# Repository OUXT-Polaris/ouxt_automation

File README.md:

# What is this?

Automation pipeline for Maritime RobotX Challenge

# What can we do with this tools.

- Setup development environment with ansible.
- Setting and manage CI toolchain to the target repository.
- Generating documentation. etc...

If you want to know more?
Please read [here.](https://ouxt-polaris.github.io/ouxt_automation/)

Developed by [OUXT-Polaris](https://www.ouxt.jp/)

# Sponsor

Our activities are made possible thanks to the support of our sponsors.

Eight Knot

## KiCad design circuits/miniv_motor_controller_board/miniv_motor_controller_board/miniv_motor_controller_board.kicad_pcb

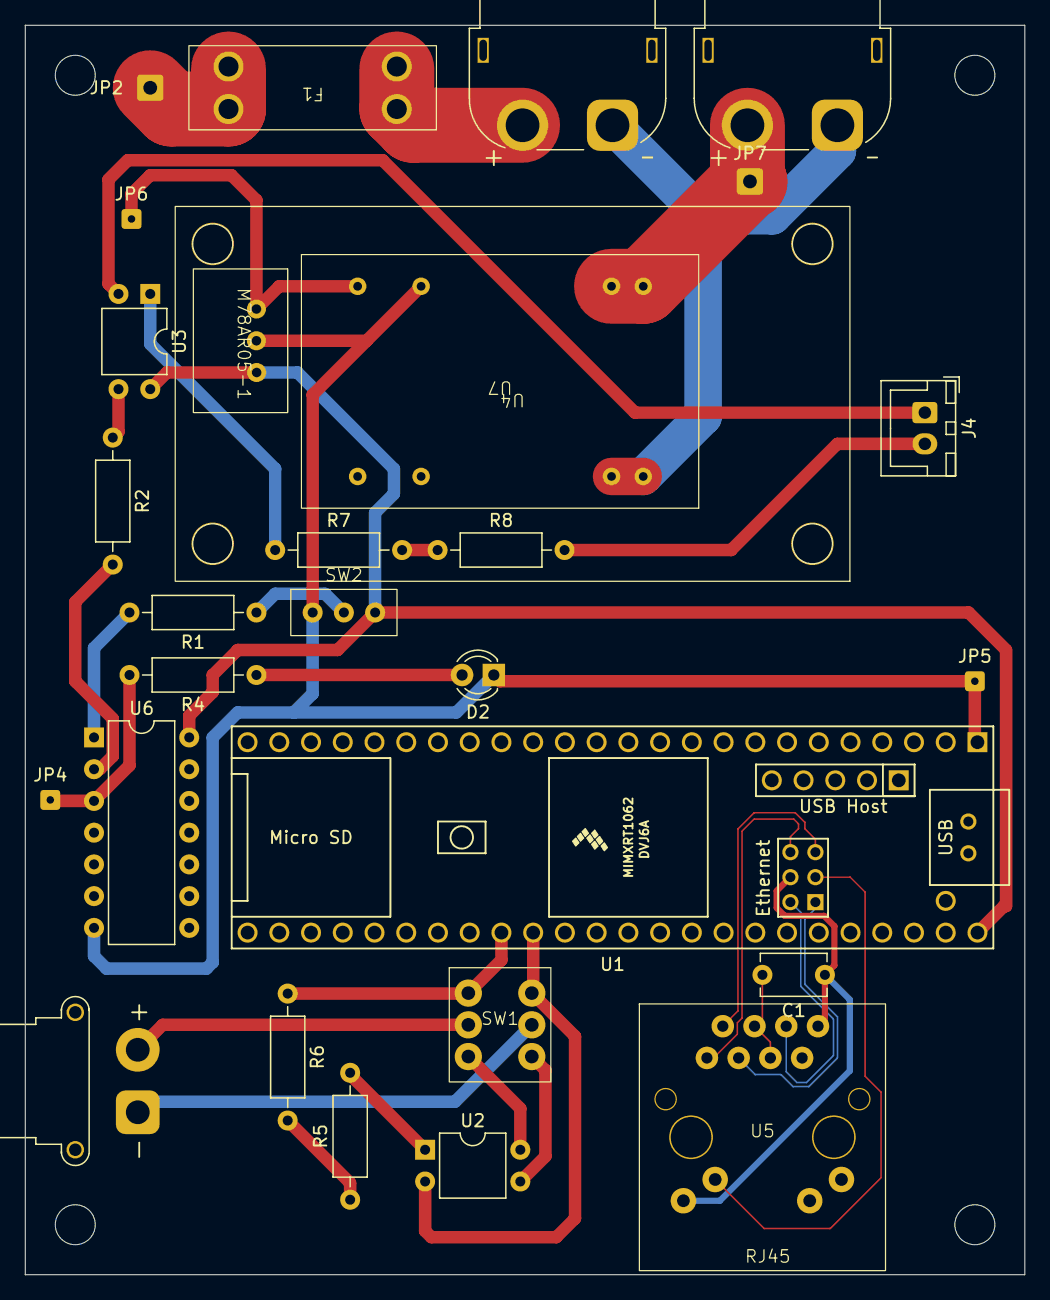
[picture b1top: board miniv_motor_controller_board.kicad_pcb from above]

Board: 2 copper layers, 80.0 x 100.0 mm, 33 parts (0 on the bottom side), 32 nets.

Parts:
C1: 0.1u; C_Disc_D5.1mm_W3.2mm_P5.00mm
D2: LED; LED_D3.0mm
F1: Fuse; 3557-15
H1, H2, H3, H4: MountingHole; MountingHole_3.2mm_M3
J1: DC_in; AMASS_XT60PW-F_1x02_P7.20mm_Horizontal
J2: T200_ESC_power; AMASS_XT60PW-F_1x02_P7.20mm_Horizontal
J3: T200_ESC_signal; AMASS_XT30PW-F_1x02_P2.50mm_Horizontal
J4: Conn_EStop_Signal; JST_XH_B2B-XH-A_1x02_P2.50mm_Vertical
JP2: Relay_NO; SolderWire-0.5sqmm_1x01_D0.9mm_OD2.1mm
JP4: Relay_SIG; SolderWire-0.1sqmm_1x01_D0.4mm_OD1mm
JP5: Relay_GND; SolderWire-0.1sqmm_1x01_D0.4mm_OD1mm
JP6: Relay_VCC; SolderWire-0.1sqmm_1x01_D0.4mm_OD1mm
JP7: Relay_COM; SolderWire-0.5sqmm_1x01_D0.9mm_OD2.1mm
M78AR05-1: M78AR05-1
R1, R2, R6, R7: 1K; R_Axial_DIN0207_L6.3mm_D2.5mm_P10.16mm_Horizontal
R4, R5, R8: 390; R_Axial_DIN0207_L6.3mm_D2.5mm_P10.16mm_Horizontal
SW1: SW_Push_DPDT; 2MD1-T2-B4-M2-Q-N
SW2: SW_disable_EStop; SS-12D00G3
U1: Teensy4.1; Teensy41
U2, U3: TLP624; DIP-4_W7.62mm
U4: AE-RELAY953B-12V
U5: RJLD-260YC1
U6: DIP-14_W7.62mm
U7: MIWI06-24S12

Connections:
+12V: JP6.1 (A), M78AR05-1.1 (Vin), U7.14 (+Vout)
GNDREF: D2.1 (K), JP5.1 (A), M78AR05-1.2 (GND), SW2.1 (A), U1.1 (GND), U6.7 (GND), U7.16 (-Vout)
GNDREF_Bat: J1.1, J2.1, U7.2 (-Vin), U7.3 (-Vin)
unnamed: C1.2, U5.4 (CT), U5.5 (CT)
unnamed: D2.2 (A), R4.1
unnamed: J1.2, JP7.1 (A), U7.22 (+Vin), U7.23 (+Vin)
unnamed: F1.1, J2.2
unnamed: J3.1, SW1.2 (B)
unnamed: J3.2, SW1.5 (B)
unnamed: J4.1, U3.2
unnamed: J4.2, R8.2
unnamed: F1.2, JP2.1 (A)
unnamed: JP4.1 (A), R4.2, U6.3 (1Y)
unnamed: M78AR05-1.3 (Vout), SW2.3 (C), U1.48 (VIN), U3.4, U6.14 (Vcc)
unnamed: R2.1, U3.3
unnamed: R5.1, R6.2
unnamed: R5.2, U2.1
unnamed: R7.1, U3.1
unnamed: R7.2, R8.1
unnamed: SW1.1 (A), U1.34 (GND), U2.2
unnamed: SW1.3 (C), U2.3
unnamed: SW1.6 (C), U2.4
unnamed: R1.1, SW2.2 (B)
unnamed: R6.1, SW1.4 (A), U1.33 (41_A17)
unnamed: U1.61 (LED), U5.10
unnamed: U1.60 (R+), U5.3 (RD+)
unnamed: U1.65 (R-), U5.6 (RD-)
unnamed: U1.63 (T+), U5.1 (TD+)
unnamed: U1.62 (T-), U5.2 (TD-)
unnamed: C1.1, U1.64 (GND), U5.8 (GND), U5.9
unnamed: R1.2, U6.1 (1A)
unnamed: R2.2, U6.2 (1B)

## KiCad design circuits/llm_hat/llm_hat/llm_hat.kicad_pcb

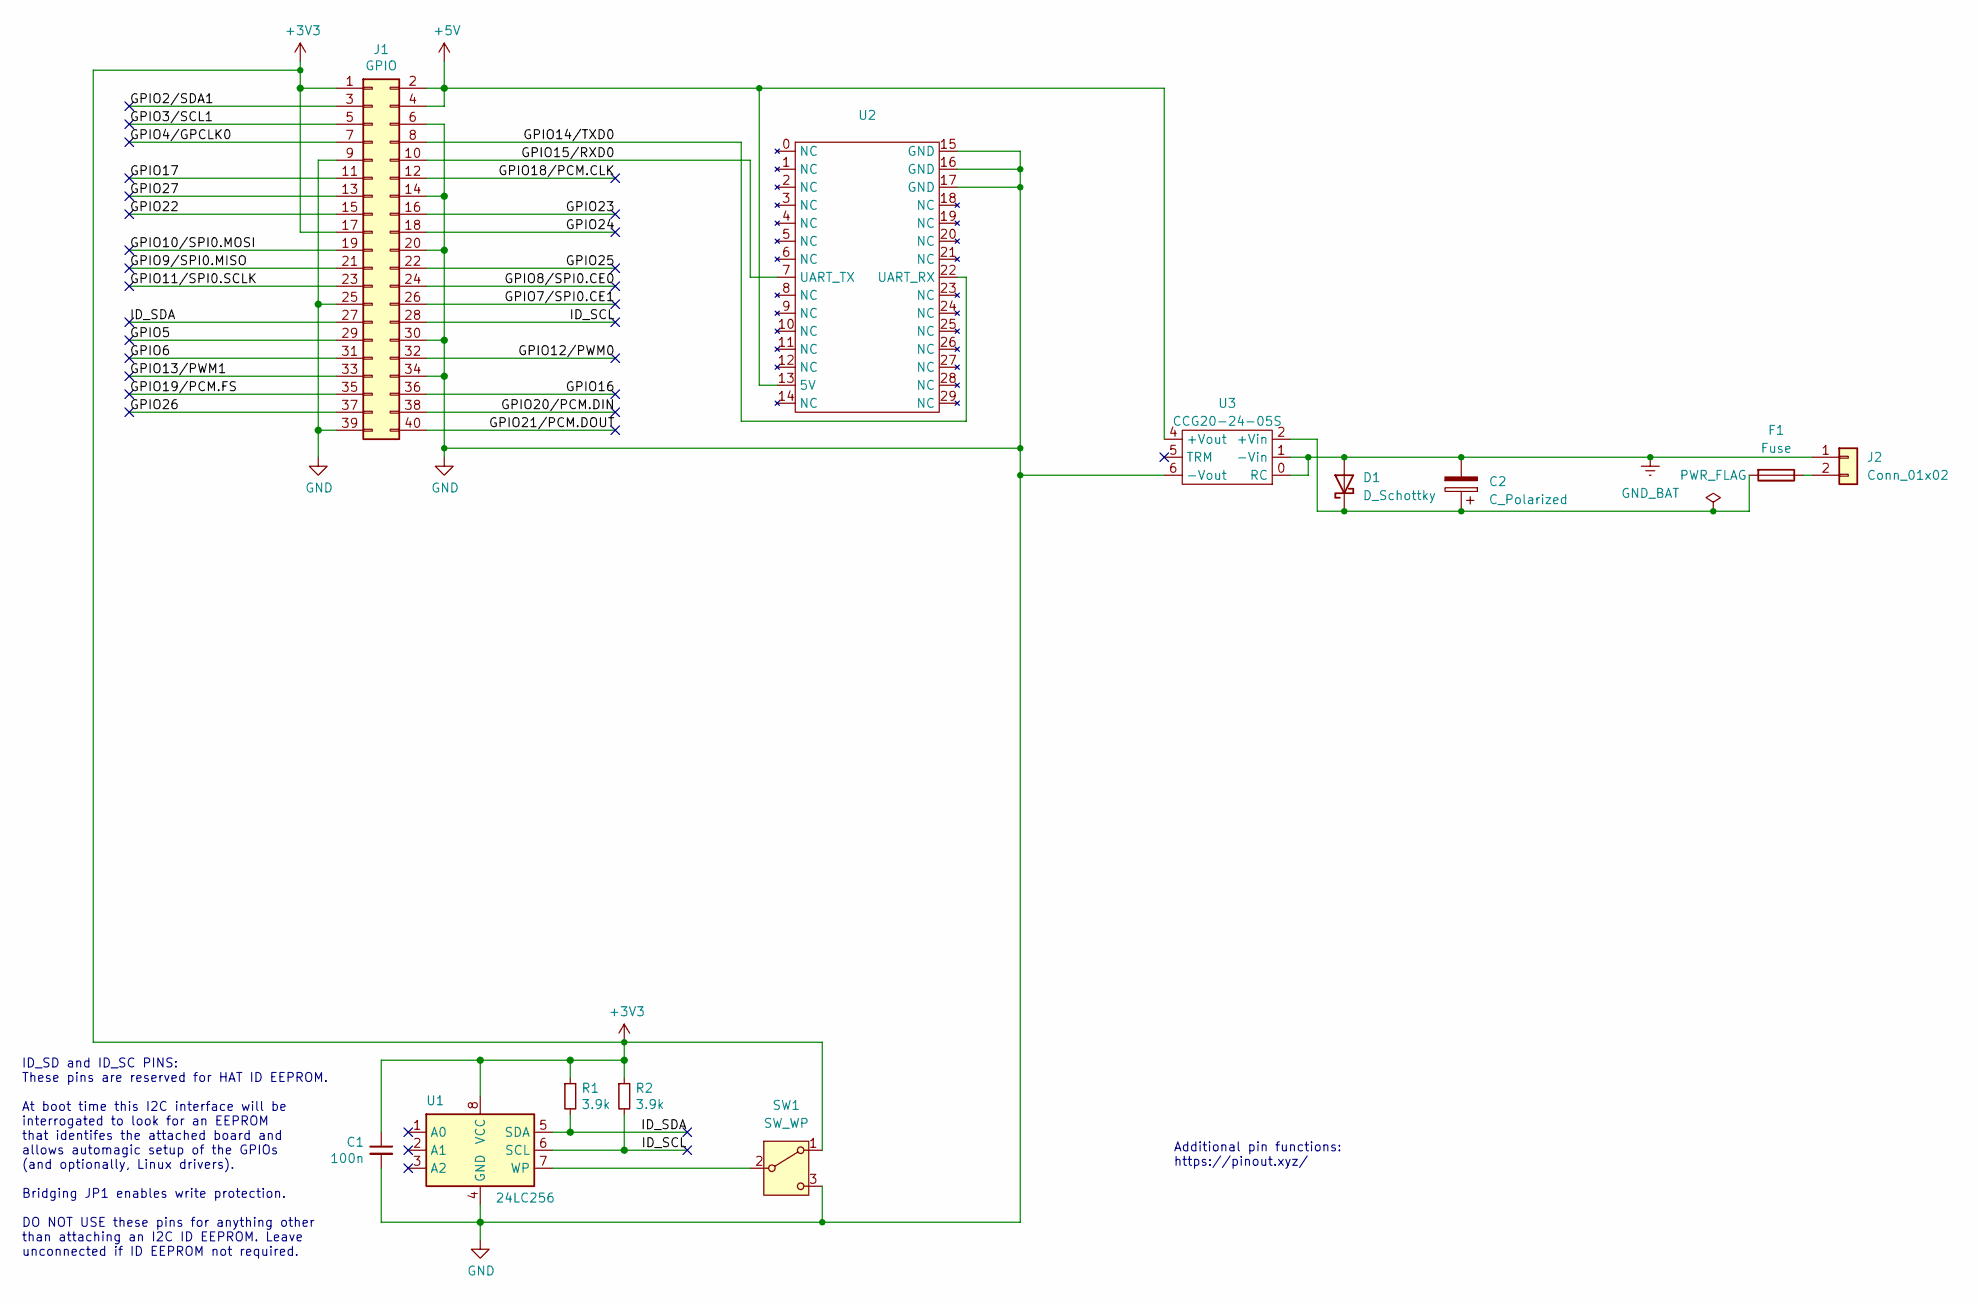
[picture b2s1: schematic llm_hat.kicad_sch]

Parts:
C1: 100n; C_Rect_L7.2mm_W4.5mm_P5.00mm_FKS2_FKP2_MKS2_MKP2
C2: C_Polarized; CP_Radial_D16.0mm_P7.50mm
D1: D_Schottky; R_Axial_DIN0207_L6.3mm_D2.5mm_P10.16mm_Horizontal
F1: Fuse; 3557-15
J1: GPIO; PinSocket_2x20_P2.54mm_Vertical
J2: Conn_01x02; AMASS_XT60PW-F_1x02_P7.20mm_Horizontal
R1, R2: 3.9k; R_Axial_DIN0207_L6.3mm_D2.5mm_P10.16mm_Horizontal
SW1: SW_WP; SS-12D00G3
U1: 24LC256; DIP-8_W7.62mm
U2: llm_module
U3: CCG20-24-05S; CCG30-24-05S

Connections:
+3V3: C1.1, J1.1, J1.17, R1.1, R2.1, SW1.1 (A), U1.8 (VCC)
+5V: J1.2, J1.4, U2.13 (5V), U3.4 (+Vout)
/GPIO2/SDA1: J1.3
/GPIO3/SCL1: J1.5
/GPIO4/GPCLK0: J1.7
/GPIO5: J1.29
/GPIO6: J1.31
/GPIO7/SPI0.CE1: J1.26
/GPIO8/SPI0.CE0: J1.24
/GPIO9/SPI0.MISO: J1.21
/GPIO10/SPI0.MOSI: J1.19
/GPIO11/SPI0.SCLK: J1.23
/GPIO12/PWM0: J1.32
/GPIO13/PWM1: J1.33
/GPIO14/TXD0: J1.8, U2.22 (UART_RX)
/GPIO15/RXD0: J1.10, U2.7 (UART_TX)
/GPIO16: J1.36
/GPIO17: J1.11
/GPIO18/PCM.CLK: J1.12
/GPIO19/PCM.FS: J1.35
/GPIO20/PCM.DIN: J1.38
/GPIO21/PCM.DOUT: J1.40
/GPIO22: J1.15
/GPIO23: J1.16
/GPIO24: J1.18
/GPIO25: J1.22
/GPIO26: J1.37
/GPIO27: J1.13
/ID_SCL: J1.28, R2.2, U1.6 (SCL)
/ID_SDA: J1.27, R1.2, U1.5 (SDA)
GND: C1.2, J1.6, J1.9, J1.14, J1.20, J1.25, J1.30, J1.34, J1.39, SW1.3 (C), U1.4 (GND), U2.15 (GND), U2.16 (GND), U2.17 (GND), U3.6 (-Vout)
GND_BAT: C2.2, D1.2 (A), J2.1, U3.0 (RC), U3.1 (-Vin)
unnamed: C2.1, D1.1 (K), F1.2, U3.2 (+Vin)
unnamed: F1.1, J2.2
unnamed: SW1.2 (B), U1.7 (WP)

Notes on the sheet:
Additional pin functions: https://pinout.xyz/
ID_SD and ID_SC PINS: These pins are reserved for HAT ID EEPROM. At boot time this I2C interface will be interrogated to look for an EEPROM that identifes the attached board and allows automagic setup of the GPIOs (and optionally, Linux drivers). Bridging JP1 enables write protection. DO NOT USE th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

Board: 2 copper layers, 16 parts (1 on the bottom side), 11 nets, no tracks yet.

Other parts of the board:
MH1, MH2, MH3, MH4: MountingHole_2.7mm_M2.5

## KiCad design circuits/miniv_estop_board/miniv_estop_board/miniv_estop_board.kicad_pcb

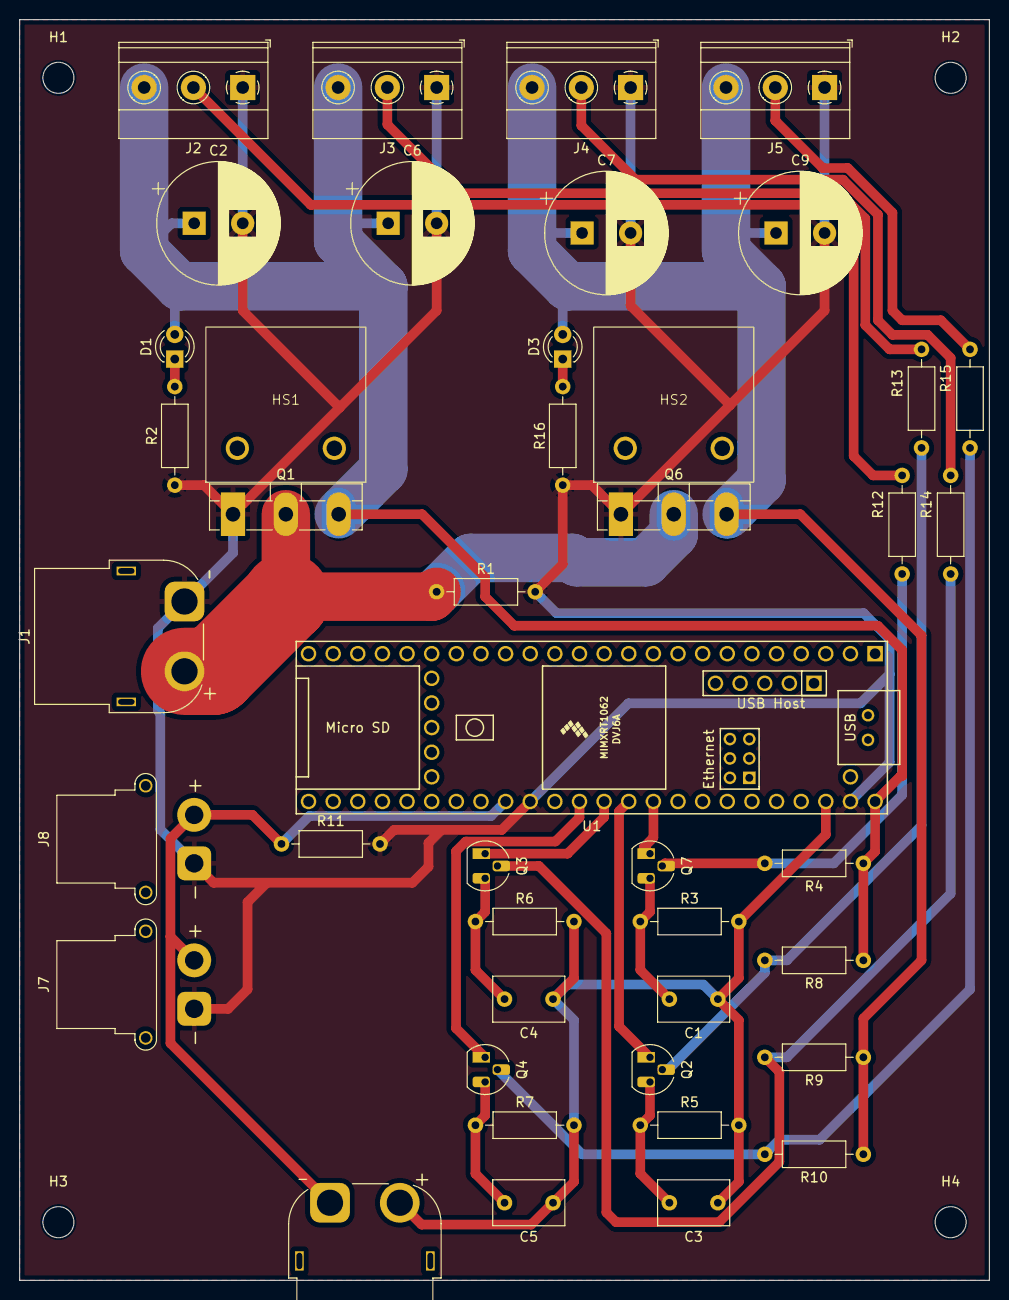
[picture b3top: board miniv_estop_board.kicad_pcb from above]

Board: 2 copper layers, 100.0 x 130.0 mm, 47 parts (0 on the bottom side), 24 nets.

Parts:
C1, C3, C4, C5: 0.1u; C_Rect_L7.2mm_W4.5mm_P5.00mm_FKS2_FKP2_MKS2_MKP2
C2, C6, C7, C9: 1000μ; CP_Radial_D12.5mm_P5.00mm
D1, D3: LED; LED_D3.0mm
H1, H2, H3, H4: MountingHole; MountingHole_3.2mm_M3
HS1, HS2: Heatsink; 16PB017-01025
J1: Conn_Main_DCDC; AMASS_XT60PW-F_1x02_P7.20mm_Horizontal
J2: Conn_neopixel_01; TerminalBlock_Phoenix_MKDS-1,5-3-5.08_1x03_P5.08mm_Horizont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
J3: Conn_neopixel_02; TerminalBlock_Phoenix_MKDS-1,5-3-5.08_1x03_P5.08mm_Horizont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
J4: Conn_neopixel_03; TerminalBlock_Phoenix_MKDS-1,5-3-5.08_1x03_P5.08mm_Horizont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
J5: Conn_neopixel_04; TerminalBlock_Phoenix_MKDS-1,5-3-5.08_1x03_P5.08mm_Horizont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
J6: EStop_button; AMASS_XT60PW-F_1x02_P7.20mm_Horizontal
J7: EStop_signal0; AMASS_XT30PW-F_1x02_P2.50mm_Horizontal
J8: EStop_signal1; AMASS_XT30PW-F_1x02_P2.50mm_Horizontal
Q1, Q6: 2SJ555-E; TO-3P-3_Vertical
Q2, Q3, Q4, Q7: NPN; TO-92L_HandSolder
R1: 1K; R_Axial_DIN0207_L6.3mm_D2.5mm_P10.16mm_Horizontal
R2, R16: 390; R_Axial_DIN0207_L6.3mm_D2.5mm_P10.16mm_Horizontal
R3, R5, R6, R7, R11: 4.7K; R_Axial_DIN0207_L6.3mm_D2.5mm_P10.16mm_Horizontal
R4, R8, R9, R10, R12, R13, R14, R15: 470; R_Axial_DIN0207_L6.3mm_D2.5mm_P10.16mm_Horizontal
U1: Teensy4.1; Teensy41

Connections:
GND: C2.2, C6.2, C7.2, C9.2, J1.1, J2.1, J3.1, J4.1, J5.1, J7.1, J8.1, Q1.1 (G), Q6.1 (G), R1.2, R2.1, R11.2, R16.1, U1.34 (GND), U1.47 (GND)
unnamed: C2.1, C6.1, D1.2 (A), J2.3, J3.3, Q1.3 (S), R4.1, R8.1, U1.48 (VIN)
unnamed: D1.1 (K), R2.2
unnamed: C7.1, C9.1, D3.2 (A), J4.3, J5.3, Q6.3 (S), R9.1, R10.1
unnamed: D3.1 (K), R16.2
unnamed: J1.2, Q1.2 (D), Q6.2 (D), R1.1
unnamed: J2.2, R12.1
unnamed: J3.2, R13.1
unnamed: J4.2, R14.1
unnamed: J5.2, R15.1
unnamed: J6.1, J7.2, J8.2, R11.1, U1.33 (41_A17)
unnamed: C1.1, C3.1, C4.1, C5.1, J6.2, R3.2, R5.2, R6.2, R7.2, U1.46 (3V3)
unnamed: C3.2, Q2.3 (B), R5.1
unnamed: Q2.2 (C), R8.2, R13.2
unnamed: Q2.1 (E), U1.38 (16_A2_RX4_SCL1)
unnamed: C4.2, Q3.3 (B), R6.1
unnamed: Q3.2 (C), R9.2, R14.2
unnamed: Q3.1 (E), U1.37 (15_A1_RX3_SPDIF_IN)
unnamed: C5.2, Q4.3 (B), R7.1
unnamed: Q4.2 (C), R10.2, R15.2
unnamed: Q4.1 (E), U1.36 (14_A0_TX3_SPDIF_OUT)
unnamed: C1.2, Q7.3 (B), R3.1
unnamed: Q7.2 (C), R4.2, R12.2
unnamed: Q7.1 (E), U1.39 (17_A3_TX4_SDA1)

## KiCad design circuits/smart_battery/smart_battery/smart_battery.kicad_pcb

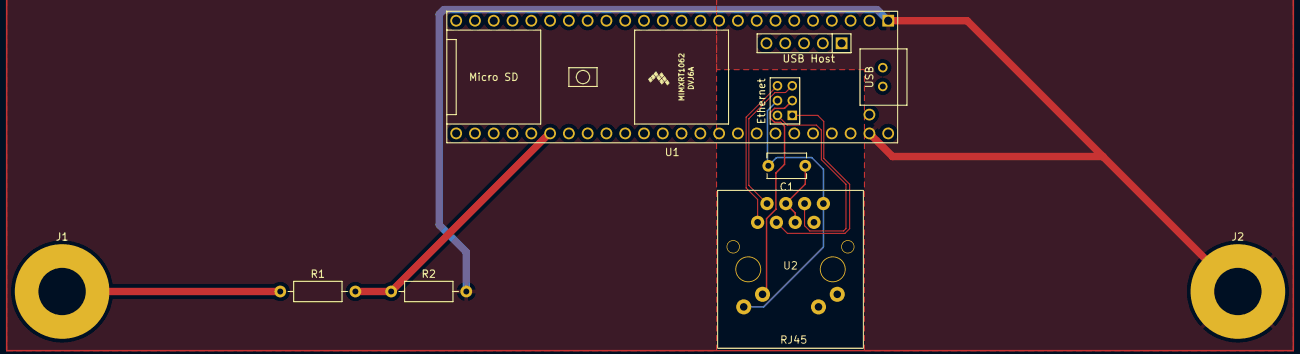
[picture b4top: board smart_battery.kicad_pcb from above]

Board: 2 copper layers, 7 parts (0 on the bottom side), 10 nets.

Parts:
C1: 0.1u; C_Disc_D5.1mm_W3.2mm_P5.00mm
J1: +12V; MountingHole_6.4mm_M6_Pad
J2: GND; MountingHole_6.4mm_M6_Pad
R1: 1K; R_Axial_DIN0207_L6.3mm_D2.5mm_P10.16mm_Horizontal
R2: 300; R_Axial_DIN0207_L6.3mm_D2.5mm_P10.16mm_Horizontal
U1: Teensy4.1; Teensy41
U2: RJLD-260YC1

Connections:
GND: J2.1, R2.2, U1.1 (GND), U1.47 (GND)
unnamed: C1.1, U2.4 (CT), U2.5 (CT)
unnamed: J1.1, R1.1
unnamed: R1.2, R2.1, U1.30 (38_CS1_IN1)
unnamed: U1.61 (LED), U2.10
unnamed: U1.60 (R+), U2.3 (RD+)
unnamed: U1.65 (R-), U2.6 (RD-)
unnamed: U1.63 (T+), U2.1 (TD+)
unnamed: U1.62 (T-), U2.2 (TD-)
unnamed: C1.2, U1.64 (GND), U2.8 (GND), U2.9

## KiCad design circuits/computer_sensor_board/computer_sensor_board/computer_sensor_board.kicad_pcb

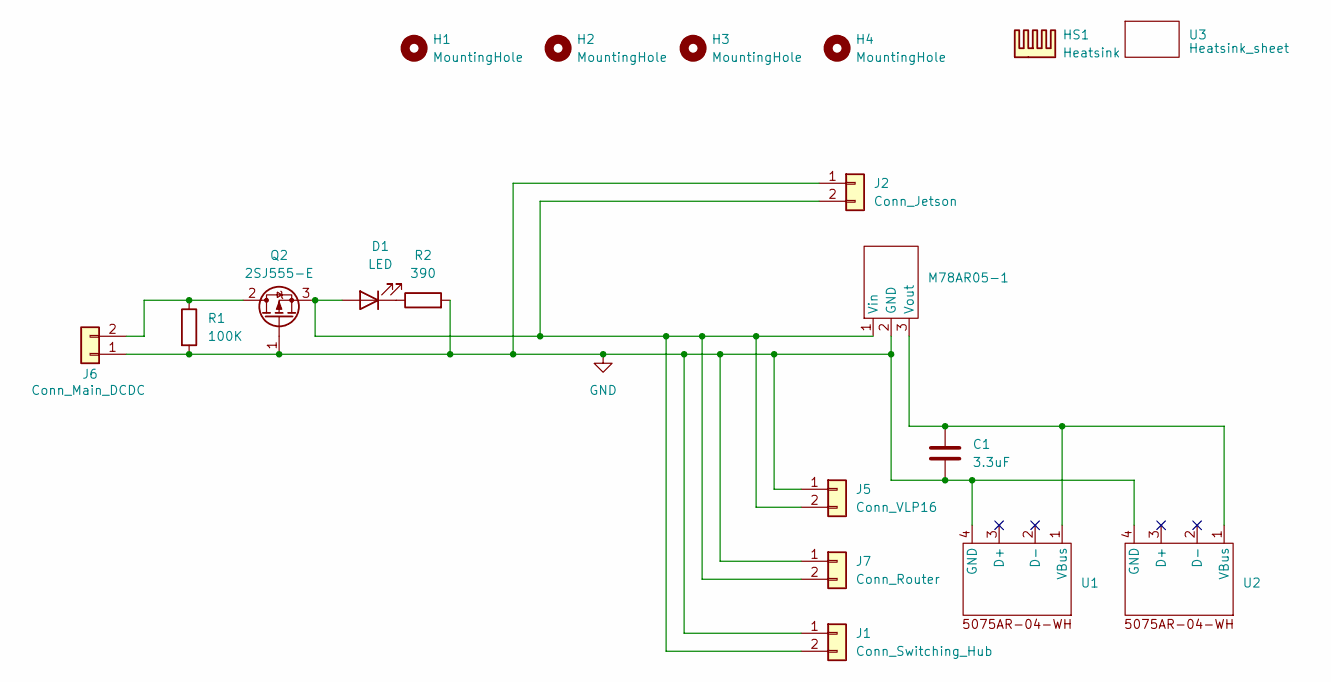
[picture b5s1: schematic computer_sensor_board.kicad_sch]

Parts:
C1: 3.3uF; C_Rect_L7.2mm_W4.5mm_P5.00mm_FKS2_FKP2_MKS2_MKP2
D1: LED; LED_D3.0mm
H1, H2, H3, H4: MountingHole; MountingHole_3.2mm_M3
HS1: Heatsink; 16PB017-01025
J1: Conn_Switching_Hub; AMASS_XT30PW-F_1x02_P2.50mm_Horizontal
J2: Conn_Jetson; AMASS_XT60PW-F_1x02_P7.20mm_Horizontal
J5: Conn_VLP16; AMASS_XT30PW-F_1x02_P2.50mm_Horizontal
J6: Conn_Main_DCDC; AMASS_XT60PW-F_1x02_P7.20mm_Horizontal
J7: Conn_Router; AMASS_XT30PW-F_1x02_P2.50mm_Horizontal
M78AR05-1: M78AR05-1
Q2: 2SJ555-E; TO-3P-3_Vertical
R1: 100K; R_Axial_DIN0207_L6.3mm_D2.5mm_P10.16mm_Horizontal
R2: 390; R_Axial_DIN0207_L6.3mm_D2.5mm_P10.16mm_Horizontal
U1, U2: 5075AR-04-WH
U3: Heatsink_sheet; TO-3PH

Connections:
GND: C1.2, J1.1, J2.1, J5.1, J6.1, J7.1, M78AR05-1.2 (GND), Q2.1 (G), R1.2, R2.2, U1.4 (GND), U2.4 (GND)
unnamed: D1.2 (A), J1.2, J2.2, J5.2, J7.2, M78AR05-1.1 (Vin), Q2.3 (S)
unnamed: D1.1 (K), R2.1
unnamed: J6.2, Q2.2 (D), R1.1
unnamed: C1.1, M78AR05-1.3 (Vout), U1.1 (VBus), U2.1 (VBus)

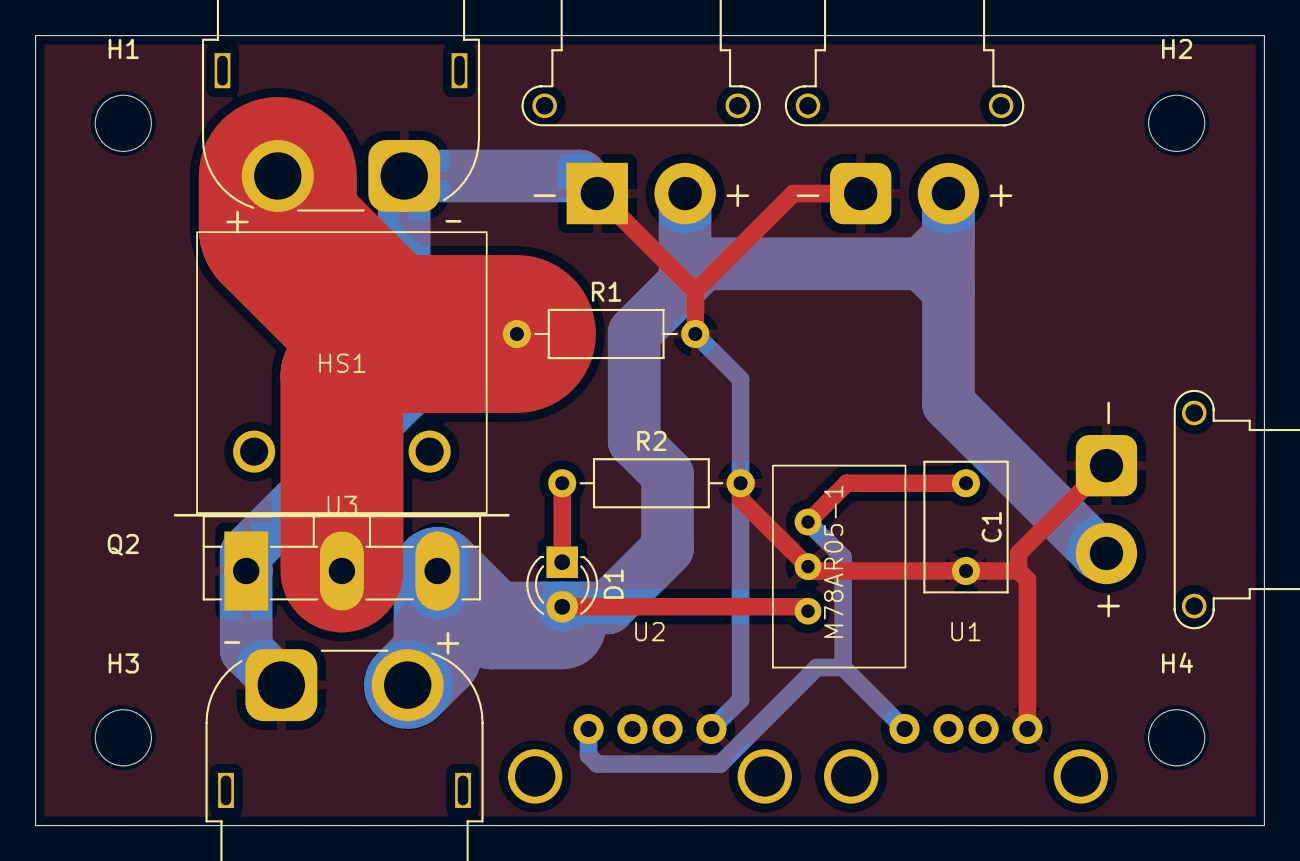
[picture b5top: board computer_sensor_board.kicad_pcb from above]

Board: 2 copper layers, 70.0 x 45.0 mm, 19 parts (0 on the bottom side), 5 nets.

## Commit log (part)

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2025-02-11 deploy: 1236caea3583ee023d5c2c500905b67245680eb4
2025-02-11 add firmware for miniv MD
2025-02-12 Feat/md firmware (#391)
    * Feature/add xhost command
    * follow upstream
    * add firmware for miniv MD
    ---------
2025-02-12 deploy: 3ca1021f6220c764943fdedde7ac94bc259d9040
2025-02-12 add firmware
2025-02-12 add debug step
2025-02-12 add buildtest for platform io firmware
2025-02-12 add name
2025-02-12 modify trigger
2025-02-12 fix workflow name
2025-02-12 modify working directory
2025-02-12 Feat/pio GitHub actions (#392)
    * update board
    * add firmware
    * add debug step
    * add buildtest for platform io firmware
    * add name
    * modify trigger
2025-02-12 follow master
2025-02-12 add protolink_drivers to the depends
2025-02-12 deploy: d135f0dd78644d0d34ef2d0ab1128e05c22d2970
2025-02-14 add estop driver farmware
2025-02-14 add config and buiid flags for right left
2025-02-14 rebert code
2025-02-14 add build and install to ignore
2025-02-14 add build and install to ignore (#396)
2025-02-14 add estop driver farmware (#394)
2025-02-14 Feat/add config and buiid flags for right left (#395)
    * add config and buiid flags for right left
    * rebert code
2025-02-14 deploy: 52fbd2395e0cfdcc875a4b930a10a75a88418f6b
2025-02-14 deploy: 72c2688fdbcbaf4c73405c7776128e6e3054b3f0
2025-02-14 deploy: c645033e51184c999d73766354f028c5d8c4f964
2025-02-14 fix: coping with the singular value zero
2025-02-14 fix: coping with the singular value zero (#397)
2025-02-14 deploy: a84127faaf2822496ada50258b7eaf531a1e58e4
2025-02-14 feat: estop signal detection and return operation
2025-02-15 feat: estop signal detection and return operation (#398)
2025-02-15 deploy: de1b5f1da2ae8b2d0f59e7b941553bbde6fe9f5a
2025-02-16 wip: add dockerfile
2025-02-16 Feat/add dockerfile for robotx_ws enviroment
2025-02-18 fix: change path and move directory
2025-02-20 feat: add heart beat listener
2025-02-20 feat: check heart beat
2025-02-20 Feat/heartbeat (#400)
2025-02-20 deploy: 0e8382cbbf9a6469bb113fd0045758ea40c2039d
2025-02-20 Feat/docker (#399)
    * wip: add dockerfile
    * Feat/add dockerfile for robotx_ws enviroment
    * fix: change path and move directory
2025-02-20 deploy: 66a30caadb8575e0e1027e5cd6379f4ff1529f62
2025-02-20 fix: delete debug remnant
2025-02-20 feat: add vscode workspace config
2025-02-21 Fix/debug remnant (#401)
    * fix: delete debug remnant
    * feat: add vscode workspace config
2025-02-21 deploy: e6e99620788d4244a48300a042935bab1c4fb7fc
2025-02-21 update ansible
2025-02-21 follow upstream
2025-02-21 update proto file
2025-02-21 modify permission
2025-02-22 feat: add gnss code
2025-02-23 feat: module, send data with ethernet
2025-02-23 feat: delete comment
2025-02-23 revert: delete serial print
2025-02-24 初めて色々追加しましたよ
    始めました
2025-02-26 Feat/mini v gnss firmware (#402)
    * feat: add gnss code
    * feat: module, send data with ethernet
    * feat: delete comment
    * revert: delete serial print
2025-02-26 deploy: 4aadb09549db43874e7acde0812a43ed0319cb26
2025-02-26 fix pb_encode error and add display out
2025-02-28 fix pb_encode error and add display out (#403)
2025-02-28 Feat/add protolink drivers (#393)
    * update board
    * add firmware
    * follow master
    * add protolink_drivers to the depends
    * update ansible
    * follow upstream
2025-02-28 deploy: ed526a86654c936bbcd43c9438853a0064f3707a
2025-02-28 deploy: 5608eabe1c824c87f587d38d62b3d7a14a5bd78b
2025-02-28 remove robotx_communication package
2025-02-28 add docker compose file
2025-02-28 update dockerfile
2025-02-28 remove robotx_communication package (#404)
2025-02-28 deploy: 9f7c4b5310e09451306678bb3326e665752d6dbc
2025-03-01 Feature/deployment (#405)
    * remove robotx_communication package
    * add docker compose file
    * update dockerfile
    ---------
2025-03-01 deploy: 26f7141ecd59e11820eab2383c31b944a8498855
2025-03-02 add depth
2025-03-02 remove prometheus_ros
2025-03-02 specify depth = 1
2025-03-02 specify depth in special packages
2025-03-02 feat: check heart beat for estop system and phsical power cutoff
2025-03-03 remove mbed
2025-03-03 update chache action version
2025-03-03 deploy: d6b7400a63ad8419d5e508424dfe99b4d29214d9
2025-03-03 add upload-artifact step to the build firmware action
2025-03-03 add matrix
2025-03-03 deploy: fb195a92b914e141e3625163a513248839767314
2025-03-03 add environment for buid matrix
2025-03-03 remove buid matrix for docker image
2025-03-03 modify pull request trigger
2025-03-03 deploy: 61aee4c12836f59f780bc294268e0a410e9d525b
2025-03-03 comment out tcp_sender and wamv_control
2025-03-03 deploy: e1666cd168adf4a5cb90e086cdf523cc52dbb179
2025-03-03 add environment to the comment
2025-03-03 fix environent name
2025-03-03 modify environment for GNSS
2025-03-03 add artifact_name
2025-03-03 udpate matrix
2025-03-03 Feature/comment out remove unused package (#411)
    * remove prometheus_ros
    * comment out tcp_sender and wamv_control
2025-03-03 deploy: c51ba4b521e9e5283c5620b7ebbf3e542440fbd9
2025-03-03 add thingsBoard to the depends
2025-03-03 add heart beat class
2025-03-03 add constructor
2025-03-03 instanciate client
2025-03-03 add python script for mqtt heartbeat
2025-03-03 add generate proto
2025-03-03 check connection
2025-03-03 enable send broadcast
2025-03-03 specify UDP port and address
2025-03-03 modify Dockerfile
2025-03-03 move directory
2025-03-03 configure action
2025-03-03 comment out description action
2025-03-03 Feature/mqtt endpoint (#413)
    * add python script for mqtt heartbeat
    * add generate proto
    * check connection
    * enable send broadcast
    * specify UDP port and address
    * modify Dockerfile
2025-03-03 deploy: e57bd6b470fe2bca77bb02cd19b652ce9bbc9ed0
2025-03-03 update docker action
2025-03-03 fix yaml
2025-03-03 fix platform
2025-03-03 modify matrix
2025-03-03 Feature/mqtt endpoint (#414)
    * add python script for mqtt heartbeat
    * add generate proto
    * check connection
    * enable send broadcast
    * specify UDP port and address
    * modify Dockerfile
2025-03-03 remove cleanup runner step
2025-03-03 deploy: 20e66c34680f9491001b7b05acddfc006903cbdf
2025-03-03 add restart option
2025-03-03 use keep alive
2025-03-03 update script
2025-03-03 Feature/mqtt endpoint (#415)
    * add python script for mqtt heartbeat
    * add generate proto
    * check connection
    * enable send broadcast
    * specify UDP port and address
    * modify Dockerfile
2025-03-03 deploy: 5cc3da8f30005fdacb4b643f1f88b2b2aa680feb
2025-03-03 update proto
2025-03-03 add new proto file
2025-03-03 add topics
2025-03-03 add motor control topic
2025-03-03 add disconnection timeout
2025-03-03 add subscribe
2025-03-03 send UDP packet
2025-03-03 add heartbeat for motor
2025-03-03 add disconnection
2025-03-03 stop motor when the motor control topic was stopped
2025-03-04 start refactoring
2025-03-04 use scheduler in heartbeat
2025-03-04 modify send_heartbeat code
2025-03-04 split code
2025-03-04 refactor code
2025-03-04 add on_message
2025-03-04 add debug line
2025-03-04 run scheduler at the beginig of loop
2025-03-04 add stop_all_motors function
2025-03-04 use stop flag
2025-03-04 stop motor when disconnected
2025-03-04 modify timeout
2025-03-04 add ground station heartbeat
2025-03-04 remove old script
2025-03-04 rename test script to ground station
2025-03-04 add TODO description
2025-03-04 add check last message function
2025-03-04 add payload as argument
2025-03-04 add apk install step
2025-03-04 add python3-dev to apk step
2025-03-04 Refactor/mqtt endpoint (#416)
    * update proto
    * add new proto file
    * add topics
    * add motor control topic
    * add disconnection timeout
    * add subscribe
2025-03-04 deploy: f4a6d01a651ad124ffcdfe0879e840b966275cf2
2025-03-04 wip: add switch logic
2025-03-04 add ground station proto
2025-03-04 deploy: 610c50443d6aa3f6f84cad459b96630f50db1c7b
2025-03-04 add nebula to the workspace
2025-03-04 update clone package
2025-03-04 update playbook
2025-03-04 remove perception_server
2025-03-04 remove simulation package
2025-03-04 specify worker
2025-03-04 change branch
2025-03-04 Feature/remove unused package (#418)
    * add nebula to the workspace
    * update clone package
    * update playbook
    * remove perception_server
    * update playbook
    * update playbook
2025-03-04 deploy: c1887cba34b49a1102ff596135609e2ca1c602fc
2025-03-04 add joy controller
2025-03-04 use new type
2025-03-04 remove unused class
2025-03-04 use new message
2025-03-04 modify endpoint
2025-03-04 fix logic
2025-03-04 remove debug line
2025-03-04 add joy controller class
2025-03-04 enable change mode
2025-03-04 mode switch
2025-03-04 stop motor heartbeat
2025-03-04 update proto message
2025-03-04 enable set mode function
2025-03-04 update endpoint
2025-03-04 set mode in motor command
2025-03-04 instanciate udp some times
2025-03-04 update schema
2025-03-04 remove unused function
2025-03-04 fix error
2025-03-04 simplify code
2025-03-04 remove scheduler
2025-03-04 remove heartbeat timeout
2025-03-04 remove ground timeout check
2025-03-04 simplify class
2025-03-04 simplifyied sample code
2025-03-05 use asyncio
2025-03-05 modify socket option
2025-03-05 modify message
2025-03-05 enable send command
2025-03-05 fix ground station
2025-03-05 use AWS
2025-03-05 update sample code
2025-03-05 simplify test code
2025-03-05 add user ID and group ID
2025-03-05 add script
2025-03-05 update docker compose yaml
2025-03-05 fix use step
2025-03-05 supress error
2025-03-05 use local image
2025-03-05 feat: apply joy stick data
2025-03-05 update logger script
2025-03-05 add forward script
2025-03-05 add argparse
2025-03-05 fix typo
2025-03-05 use docker compose for udp forward
2025-03-05 fix: import path
2025-03-05 feat: serial print
2025-03-05 add default
2025-03-05 update docker compose
2025-03-05 fix: manual mode
2025-03-05 update setting
2025-03-05 add udp_forwarder package
2025-03-05 update directory
2025-03-05 add new python package
2025-03-05 remove apk install step
2025-03-05 remove network_mode
2025-03-05 update address
2025-03-05 use github actions to build image
2025-03-05 Fix/mqtt endpoint (#421)
    * wip: add switch logic
    * add nebula to the workspace
    * update clone package
    * update playbook
    * remove perception_server
    * update playbook
2025-03-05 deploy: f8764e03d0e2b3e0271380e87365333232ec10f9
2025-03-06 deploy: 61eb13352cbeb4bdfe21333badd03687cd29f19e
2025-03-06 update docker image
2025-03-06 Feature/add amd64 logger (#420)
    * add nebula to the workspace
    * update clone package
    * update playbook
    * remove perception_server
    * update playbook
    * update playbook
2025-03-06 deploy: 850b90e3436455689aaab7cbdcad502475cf5762
2025-03-06 add logger setting
2025-03-06 deploy: f2273993f4344bdf997312e4447120127a859fe6
2025-03-07 get imu data && send data with udp
2025-03-08 bit fix
2025-03-09 Update mini_v.code-workspace
2025-03-09 add nebula to the workspace (#417)
    * add nebula to the workspace
    * update clone package
    * update playbook
    ---------
2025-03-09 deploy: 32b7c305ccfa6a721742381c24b1ff64b30ccb3c
2025-03-09 get imu data && send data with udp (#422)
    * get imu data && send data with udp
    * bit fix
    * Update mini_v.code-workspace
    ---------
2025-03-09 deploy: 2201a02d8ebe3038469934fcc90dcadbbb2e4bfe
2025-03-09 update logging script
2025-04-21 Create Fujioka_ga_Tukuri_mashita
2025-09-03 feat: revert fujioka commit
2025-09-03 fix: python version
2025-09-04 feat: upgrade kicad version
2025-09-04 fix: ERC error
2025-09-05 fix: docker image tag
2025-09-05 update timeout
2025-09-05 fix: kicad build timeout
2025-09-05 deploy: 3d4931715031e011f6a4c383f5d398e789937d1e
2025-09-10 feat: disable vrx docker build action
2025-09-12 deploy: c24853b90bcd96a2e6853afca11d4d2d7b594e3d
2026-06-27 add sponsor logo
2026-06-27 Update README.md
    add the sponsor section
2026-06-27 fix: CVE-2026-41066 security vulnerability
    Automated dependency upgrade by OrbisAI Security
